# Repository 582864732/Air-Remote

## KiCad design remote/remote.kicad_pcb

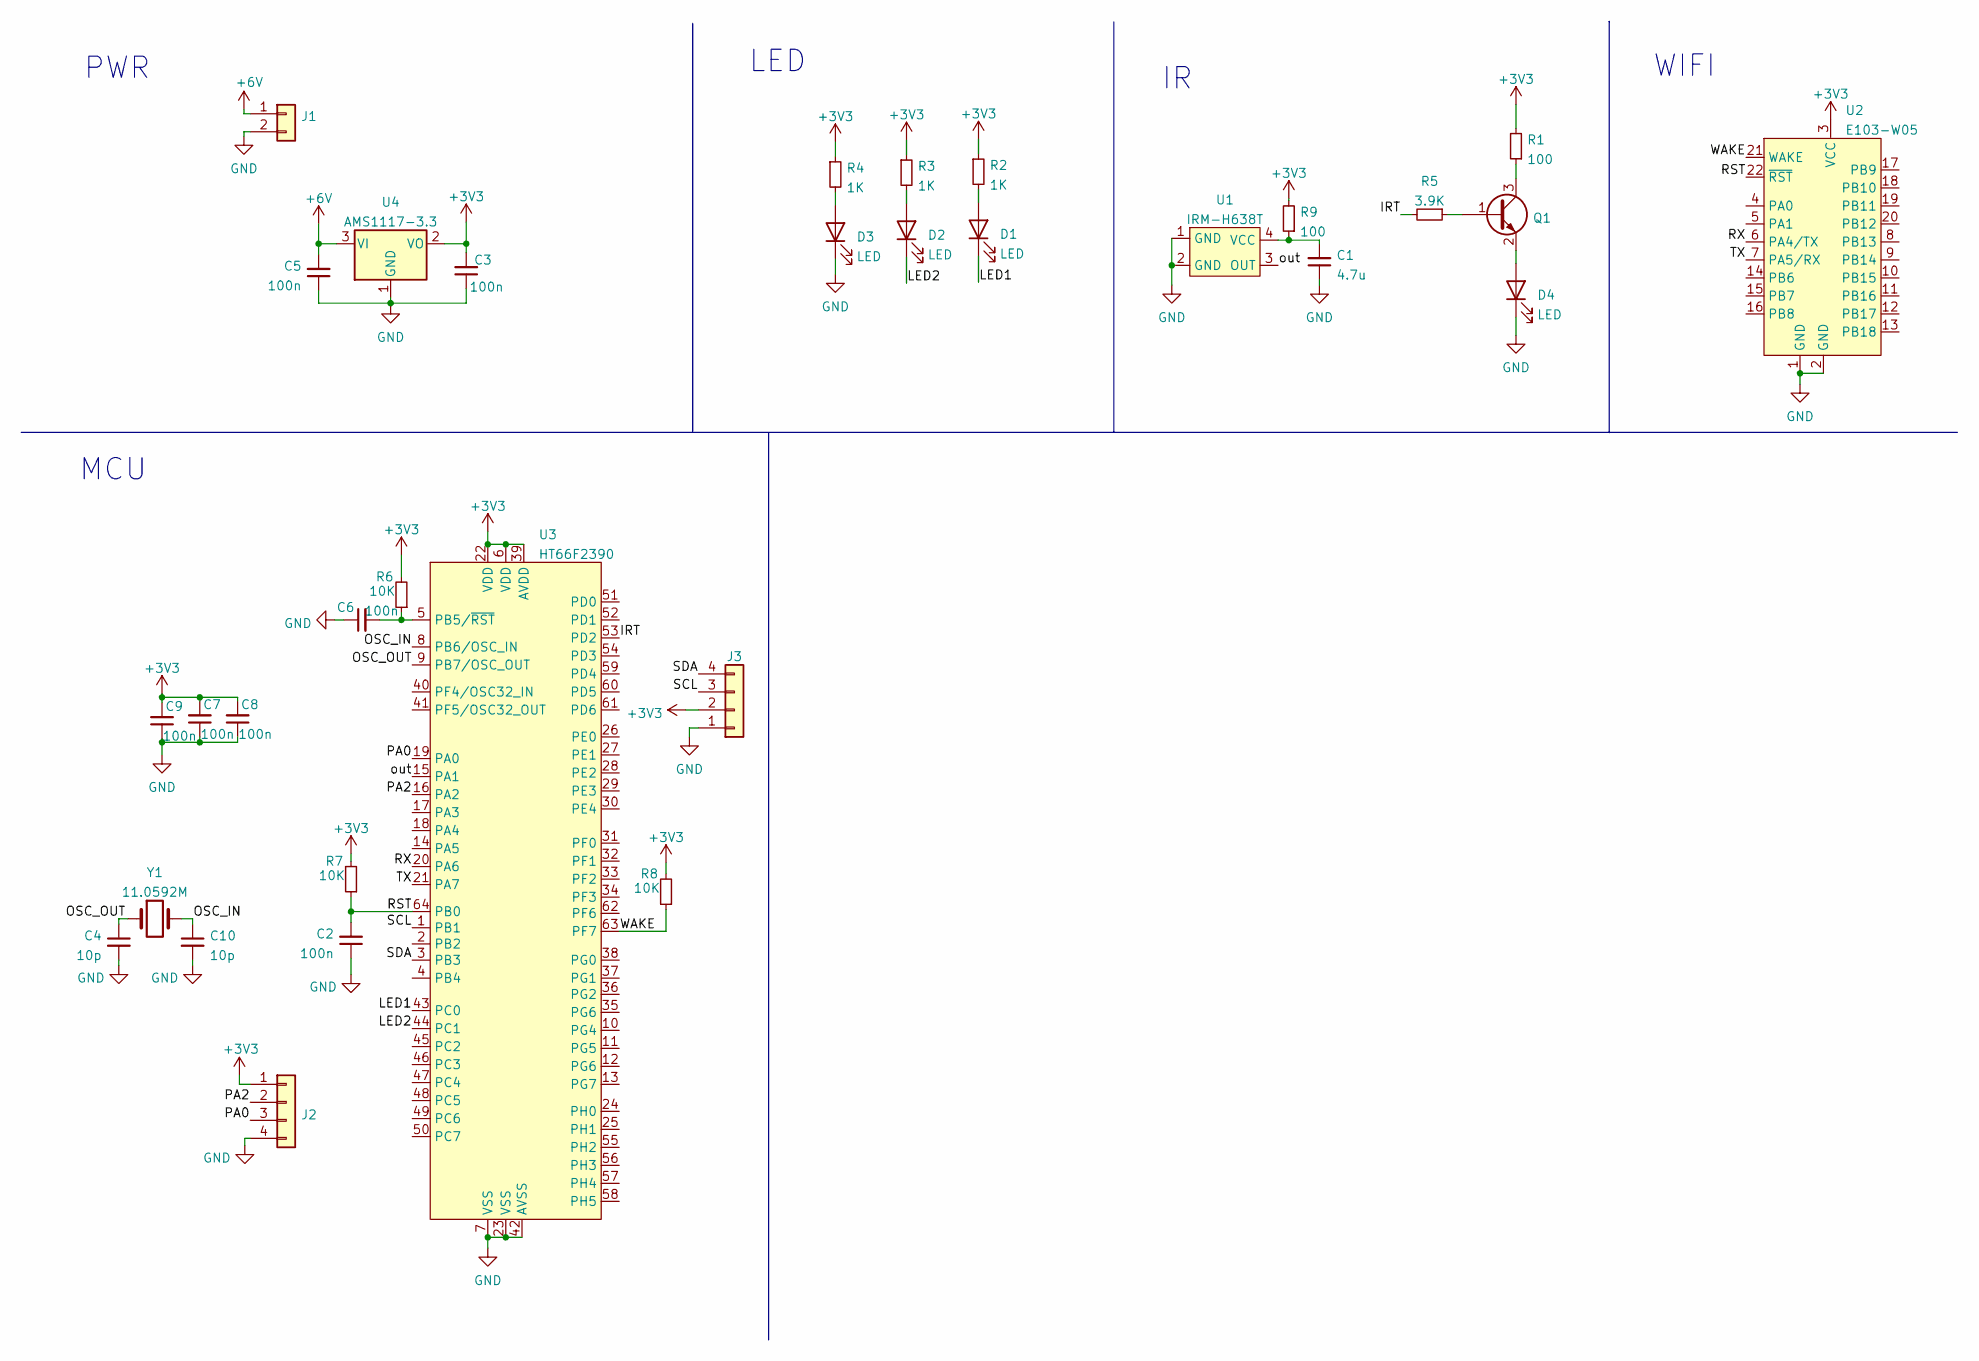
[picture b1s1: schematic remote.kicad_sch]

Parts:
C1: 4.7u; C_0603_1608Metric
C2, C3, C5, C6, C7, C8, C9: 100n; C_0603_1608Metric
C4, C10: 10p; C_0603_1608Metric
D1, D2, D3: LED; LED_0603_1608Metric
D4: LED; LED 3528
J1: Conn_01x02; PinHeader_1x02_P2.54mm_Vertical
J2, J3: Conn_01x04; PinHeader_1x04_P2.54mm_Vertical
Q1: Q_NPN_BEC; SOT-23
R1, R9: 100; R_0603_1608Metric
R2, R3, R4: 1K; R_0603_1608Metric
R5: 3.9K; R_0603_1608Metric
R6, R7, R8: 10K; R_0603_1608Metric
U1: IRM-H638T
U2: E103-W05
U3: HT66F2390; LQFP-64_7x7mm_P0.4mm
U4: AMS1117-3.3; SOT-223-3_TabPin2
Y1: 11.0592M; Crystal_HC49-4H_Vertical

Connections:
+3V3: C3.2, C7.2, C8.2, C9.2, J2.1, J3.2, R1.2, R2.1, R3.1, R4.1, R6.2, R7.2, R8.2, R9.2, U2.3 (VCC), U3.6 (VDD), U3.22 (VDD), U3.39 (AVDD), U4.2 (VO)
+6V: C5.2, J1.1, U4.3 (VI)
/IRT: R5.2, U3.53 (PD2)
/LED1: D1.1 (K), U3.43 (PC0)
/LED2: D2.1 (K), U3.44 (PC1)
/OSC_IN: C10.1, U3.8 (PB6/OSC_IN), Y1.2
/OSC_OUT: C4.1, U3.9 (PB7/OSC_OUT), Y1.1
/PA0: J2.3, U3.19 (PA0)
/PA2: J2.2, U3.16 (PA2)
/RST: C2.2, R7.1, U2.22 (~RST), U3.64 (PB0)
/RX: U2.6 (PA4/TX), U3.20 (PA6)
/SCL: J3.3, U3.1 (PB1)
/SDA: J3.4, U3.3 (PB3)
/TX: U2.7 (PA5/RX), U3.21 (PA7)
/WAKE: R8.1, U2.21 (WAKE), U3.63 (PF7)
/out: U1.3 (OUT), U3.15 (PA1)
GND: C1.1, C2.1, C3.1, C4.2, C5.1, C6.1, C7.1, C8.1, C9.1, C10.2, D3.1 (K), D4.1 (K), J1.2, J2.4, J3.1, U1.1 (GND), U1.2 (GND), U2.1 (GND), U2.2 (GND), U3.7 (VSS), U3.23 (VSS), U3.42 (AVSS), U4.1 (GND)
unnamed: C1.2, R9.1, U1.4 (VCC)
unnamed: C6.2, R6.1, U3.5 (PB5/~RST)
unnamed: D1.2 (A), R2.2
unnamed: D2.2 (A), R3.2
unnamed: D3.2 (A), R4.2
unnamed: D4.2 (A), Q1.2 (E)
unnamed: Q1.1 (B), R5.1
unnamed: Q1.3 (C), R1.1

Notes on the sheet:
LED
PWR
WIFI
MCU

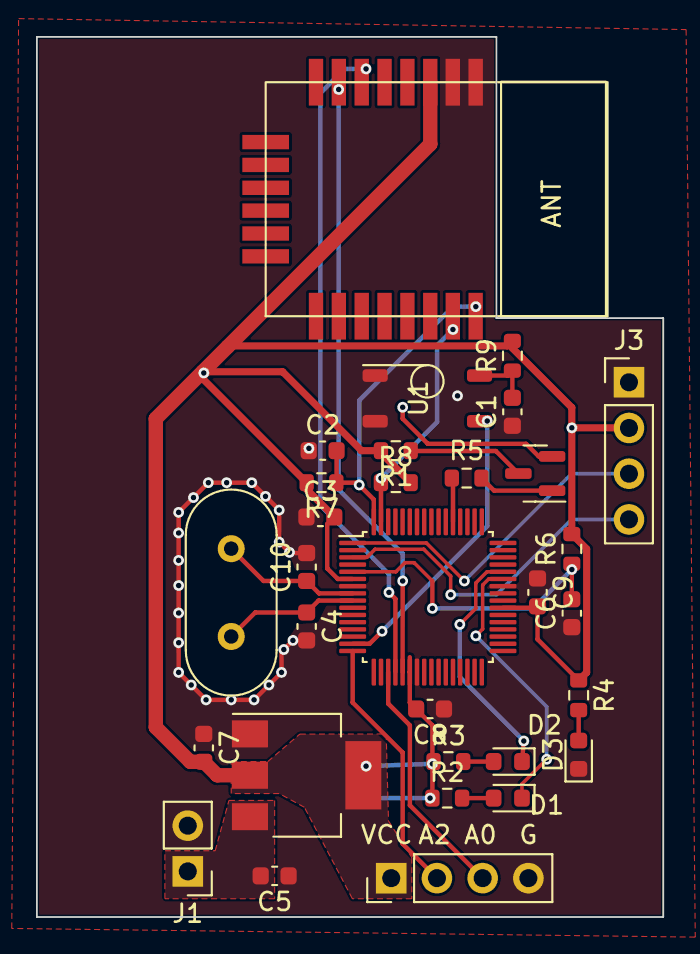
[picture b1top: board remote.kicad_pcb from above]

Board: 2 copper layers, 34.8 x 48.9 mm, 32 parts (1 on the bottom side), 25 nets.

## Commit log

2022-04-04 complete PCB
2022-04-16 add code and finish inferred transmit and receive with NEC
2022-04-16 ESP transmint and receive
2022-04-22 complete simulator and logic
2022-05-19 final code
